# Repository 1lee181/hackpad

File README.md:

# Hackpad

This is my hardware design repo for the **[Hack Club Hackpad](https://hackpad.hackclub.com/)**, a macropad built using the Seeed XIAO RP2040.

## Design

### Schematic

### PCB

### Case

## Bill of Materials (BOM)

| Qty | Name                       |
| --- | -------------------------- |
| 1   | Case top + bottom          |
| 1   | PCB                        |
| 1   | Seeed Studio XIAO RP2040   |
| 1   | 128x32 I2C OLED screen     |
| 5   | SK6812MINI-E LEDs          |
| 5   | Cherry MX-style switches   |
| 5   | Blank DSA white keycaps    |
| 1   | EC11 rotary encoder + knob |
| 4   | M3x16mm screws             |
| 4   | M3x5mx4mm heatset inserts  |

## Credits

(To be added).

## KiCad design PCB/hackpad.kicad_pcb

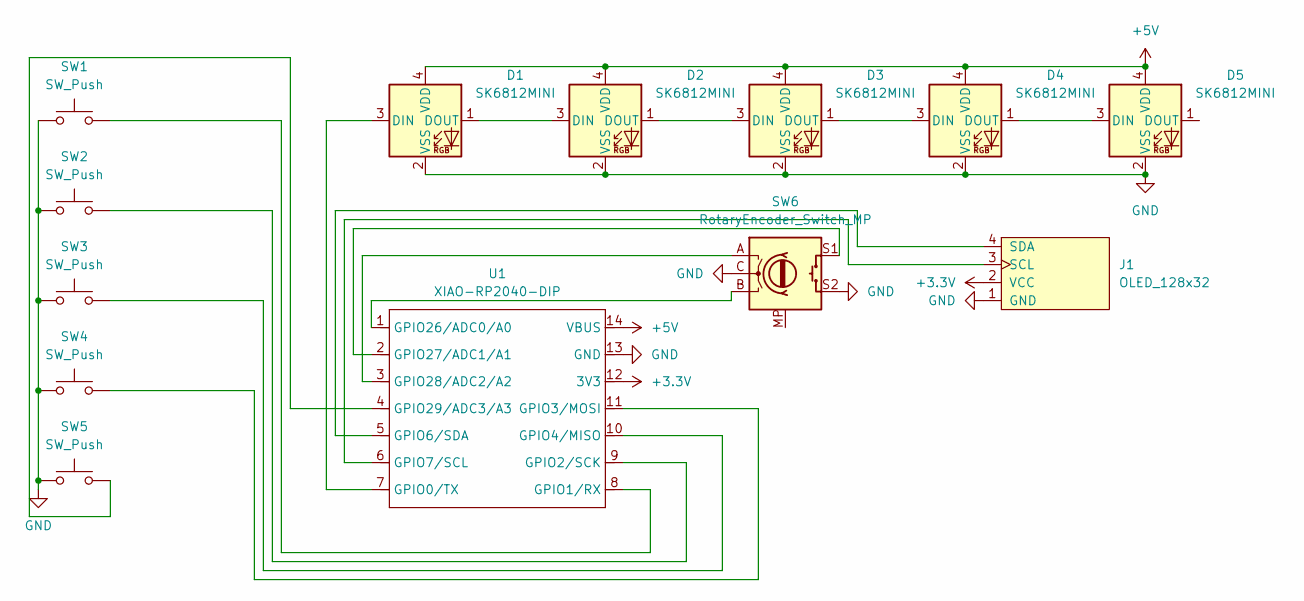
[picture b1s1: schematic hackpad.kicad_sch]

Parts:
D1, D2, D3, D4, D5: SK6812MINI; MX_SK6812MINI-E
J1: OLED_128x32
SW1, SW2, SW3, SW4, SW5: SW_Push; SW_Cherry_MX_1.00u_PCB
SW6: RotaryEncoder_Switch_MP; RotaryEncoder_Alps_EC11E-Switch_Vertical_H20mm
U1: XIAO-RP2040-DIP

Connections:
+3.3V: J1.2 (VCC), U1.12 (3V3)
+5V: D1.4 (VDD), D2.4 (VDD), D3.4 (VDD), D4.4 (VDD), D5.4 (VDD), U1.14 (VBUS)
GND: D1.2 (VSS), D2.2 (VSS), D3.2 (VSS), D4.2 (VSS), D5.2 (VSS), J1.1 (GND), SW1.1, SW2.1, SW3.1, SW4.1, SW5.1, SW6.C, SW6.S2, U1.13 (GND)
unnamed: D1.3 (DIN), U1.7 (GPIO0/TX)
unnamed: D1.1 (DOUT), D2.3 (DIN)
unnamed: D2.1 (DOUT), D3.3 (DIN)
unnamed: D3.1 (DOUT), D4.3 (DIN)
unnamed: D4.1 (DOUT), D5.3 (DIN)
unnamed: J1.3 (SCL), U1.6 (GPIO7/SCL)
unnamed: J1.4 (SDA), U1.5 (GPIO6/SDA)
unnamed: SW1.2, U1.8 (GPIO1/RX)
unnamed: SW2.2, U1.9 (GPIO2/SCK)
unnamed: SW4.2, U1.11 (GPIO3/MOSI)
unnamed: SW3.2, U1.10 (GPIO4/MISO)
unnamed: SW6.B, U1.1 (GPIO26/ADC0/A0)
unnamed: SW6.S1, U1.2 (GPIO27/ADC1/A1)
unnamed: SW6.A, U1.3 (GPIO28/ADC2/A2)
unnamed: SW5.2, U1.4 (GPIO29/ADC3/A3)

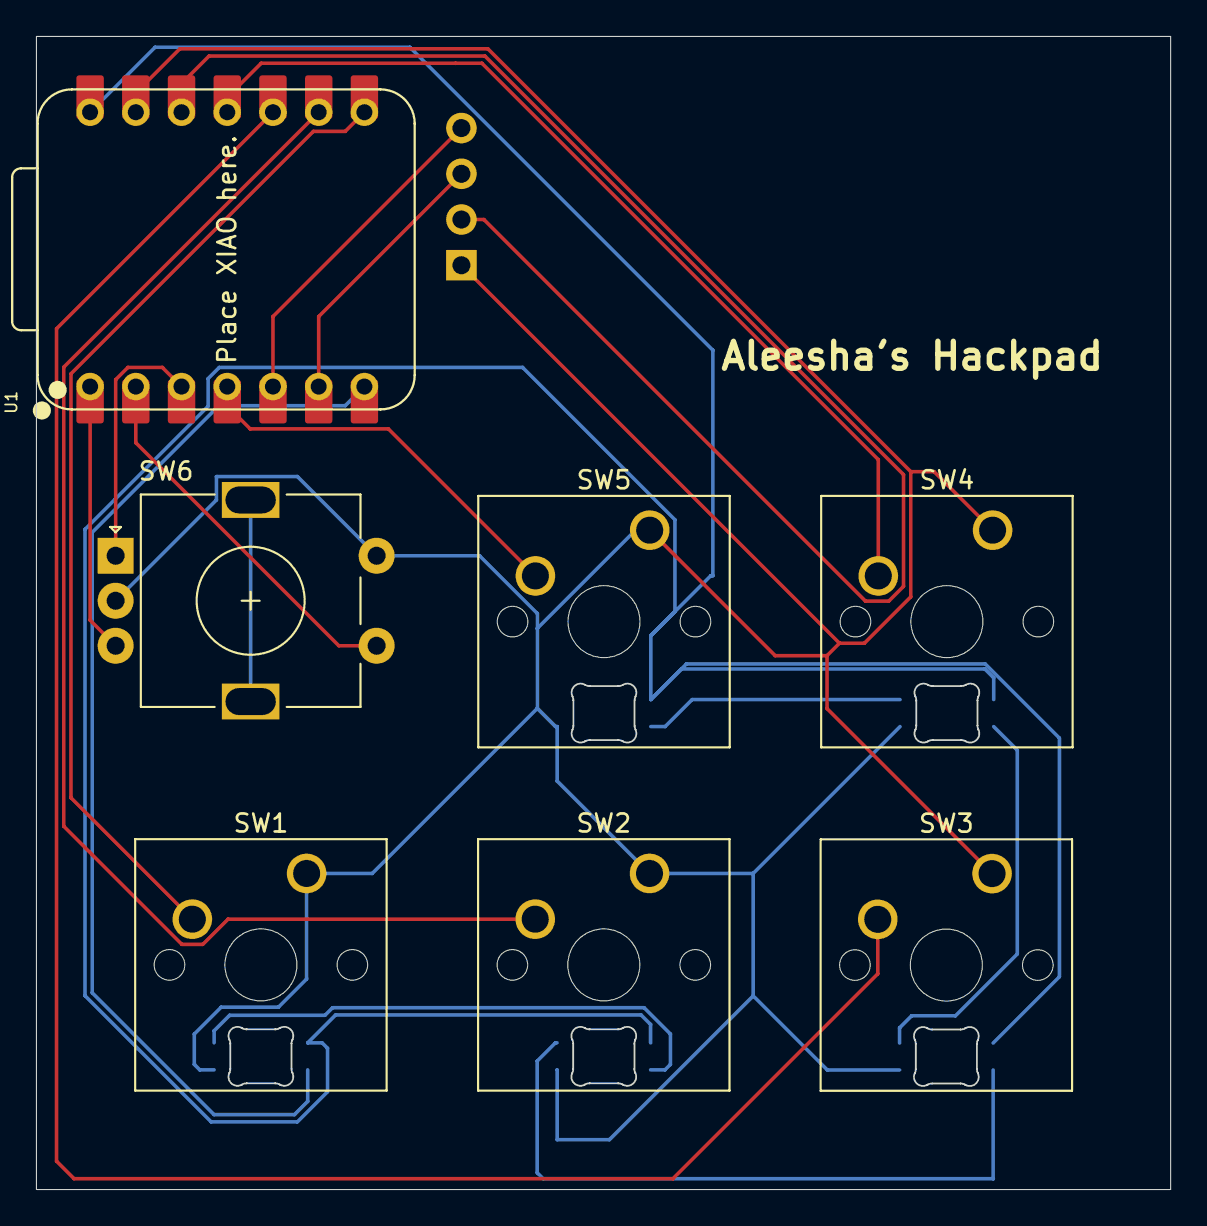
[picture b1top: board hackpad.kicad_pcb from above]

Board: 2 copper layers, 63.0 x 64.1 mm, 13 parts (0 on the bottom side), 18 nets.

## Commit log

2025-07-19 Create test
2025-08-01 Rename Screenshot (353).png to schematic.png
2025-08-01 Rename Screenshot (352).png to pcb.png
2025-08-01 Create Firmware
2025-08-02 Rename hackpad-gerbers.zip to gerbers.zip
2025-08-02 Rename Screenshot (370).png to case.png
